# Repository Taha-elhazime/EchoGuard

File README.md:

# EchoGuard

EchoGuard is a security system that is meant to be more efficient than conventional cameras. The main part is a camera turret which is ceiling mounted and uses microphones in order to detect suspicious activity and lock on to it. It also uses a wall mounted ultrasonic sensor to detect anyone who walks past a certain line using bluetooth to transmit the data.  
Demo video: 

## What is included

This project includes the Cad files for the ultrasonic wall sensor and the turret demo as it is not ceiling mounted, along with the 3mf files in order to print them.
It also includes the codes to use the turret "main_v2.py" is the stable version which tracks the person's face using mediapipe, calculates the bearing of when the face was last seen and the offset from the center (dy and dx) and sends it to the arduino through serial communication. "main_v3" is an experimental version which does not work properly, where I tried to implement ROI in order to increase the speed at which mediapipe analyzed the images by reducing the load. The codes to upload to the microcontrollers are also included.
Before 3d printing the whole thing, I included 3mf files in order to test the snap fit of the ultrasonic sensor "snap_fit_test", along with "bearing_test" as the size of the bearings varies and the project uses bearings for the rotating base.
It also includes a simple pcb that would replace the breadboard and messy jumper wires  

## How to recreate the project

The circuits are quite simple but here are schematics nontheless  

1. Use Arduino IDE in order to upload the code "EchoGaurd" for the arduino and note down the COM port used.

2. Use your code editor to update the port number in line the 8th line 
arduino = serial.Serial("COM3", 115200) change the number 3 with your port. 

3. Install the libraries mediapipe, opencv, pyserial, and numpy by running these comands in the terminal
```sh
pip install opencv-python
pip install mediapipe
pip install pyserial
pip install numpy
```

4. After 3d printing the parts, put the bearings in their holder, the bearing should have a diameter greater than the holder however try and make at least hald the bearing inside the holder.

5. Snap fit the servo at the base and either change the CAD file to fit your servo or use hot glue to connect it to the top part.

6. snap fit the tilt servo onto the top part and hot glue the camera holder and tape the camera (or adjust for a tight fit)

7. Ensure the servos are well oriented 

8. With the arduino IDE closed run the python script "main_v2" 
The demo should be up and running tracking your face, looking for it when out of frame, and returning to idle mode if it doesn't find you!

9. Hot glue a lazer if you want to see how dead accurate it is but be careful with your eyes!

10. In order to use the sensor simply snap fit the switch an solder the connections to your esp32, and close the box.

11. If you want the turret to look at the sensor when triggered use the "EchoGuard_sensor" version on your arduino and the python script "main_v2_sens"
In case of a "Port is busy" error simply close the python script
Also using the library manager install the following libraries:
Ultrasonic by Erick Simões
BluetoothSerial by Henry Abrahamsen

12. Update the sens_X and sens_Y angles to match the position of your sensor 

## Use pf AI
AI wasn't used in any major part of the project, ChatGpt was used to brainstorm and minor debugging in the python scripts. The CAD and PCB design along with the electronics and firmware were totally AI free.

## Tech Stack

### Software
- Python
- OpenCV
- MediaPipe
- Arduino IDE (C++)
- KiCad 
- Fusion 360
### Hardware
- Arduino Uno R4
- ESP32
- HC-SR04 Ultrasonic Sensor
- USB Webcam
- 2 pcs Servo Motors

## How it was made
The project started by designing the turret, the main issue was how I could make a rotating base that would be controlled with a servo. The issue was solved by using bearings. After testing the bearing holders I printed the base and the top parts.
The wiring was made using a breadboard before designing a pcb due to the connections breaking as the turret would rotate.
The software was then developed in Python using OpenCV and MediaPipe to detect the face offset from the center of the camera (dx and dy) along with the calculation of the bearing of when the face was last seen. Using trigonometry was necessery otherwise the camera would drift linearly to a corner.
A v3 version was made to optimize the code using ROI however it wasnt successful and I kept it for others to further improve it.

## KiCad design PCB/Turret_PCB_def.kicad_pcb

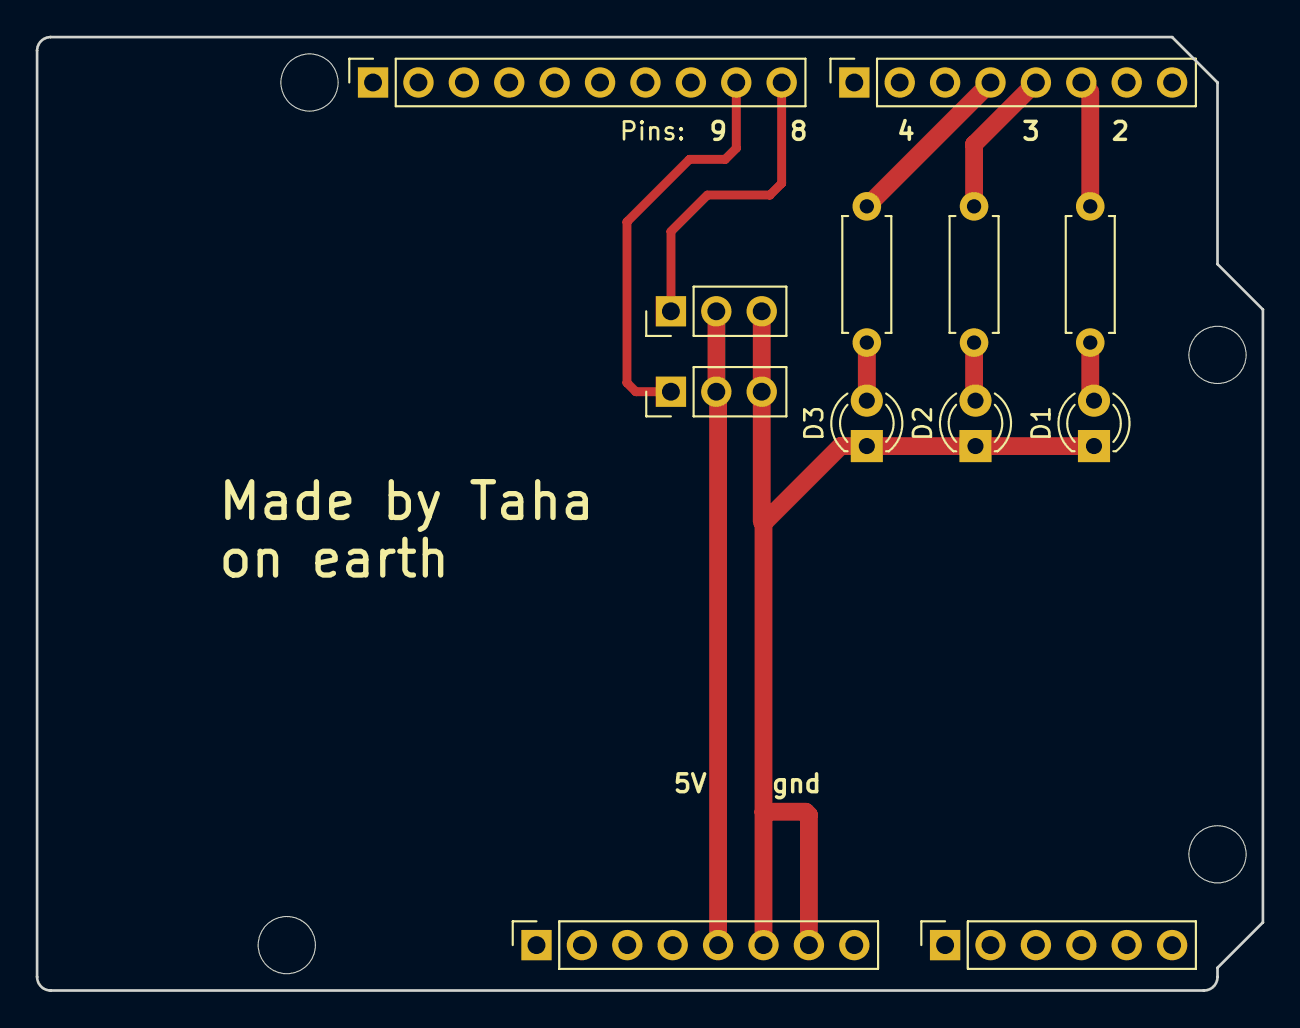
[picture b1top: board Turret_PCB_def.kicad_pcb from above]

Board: 2 copper layers, 68.6 x 53.3 mm, 16 parts (0 on the bottom side), 10 nets.

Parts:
D1, D2, D3: LED; LED_D3.0mm
J1: Power; PinSocket_1x08_P2.54mm_Vertical
J2: Digital/PWM; PinSocket_1x10_P2.54mm_Vertical
J3: Analog; PinSocket_1x06_P2.54mm_Vertical
J4: Digital/PWM; PinSocket_1x08_P2.54mm_Vertical
M1, M2: Motor_Servo; PinHeader_1x03_P2.54mm_Vertical
MH1, MH2, MH3, MH4: MountingHole_3.2mm
R1, R2, R3: 220; R_Axial_DIN0207_L6.3mm_D2.5mm_P7.62mm_Horizontal

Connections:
+5V: J1.5, M1.2 (+), M2.2 (+)
/2: J4.6, R1.2
/4: J4.4, R3.2
/8: J2.10, M1.1 (PWM)
/*3: J4.5, R2.2
/*9: J2.9, M2.1 (PWM)
GND: D1.1 (K), D2.1 (K), D3.1 (K), J1.6, J1.7, M1.3 (-), M2.3 (-)
unnamed: D1.2 (A), R1.1
unnamed: D2.2 (A), R2.1
unnamed: D3.2 (A), R3.1
